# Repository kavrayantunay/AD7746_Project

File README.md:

# AD7746_Project
I shared this project in PCBWay community, if you want to get this project please check the link "https://www.pcbway.com/project/shareproject/AD7746_Project_023b445f.html"

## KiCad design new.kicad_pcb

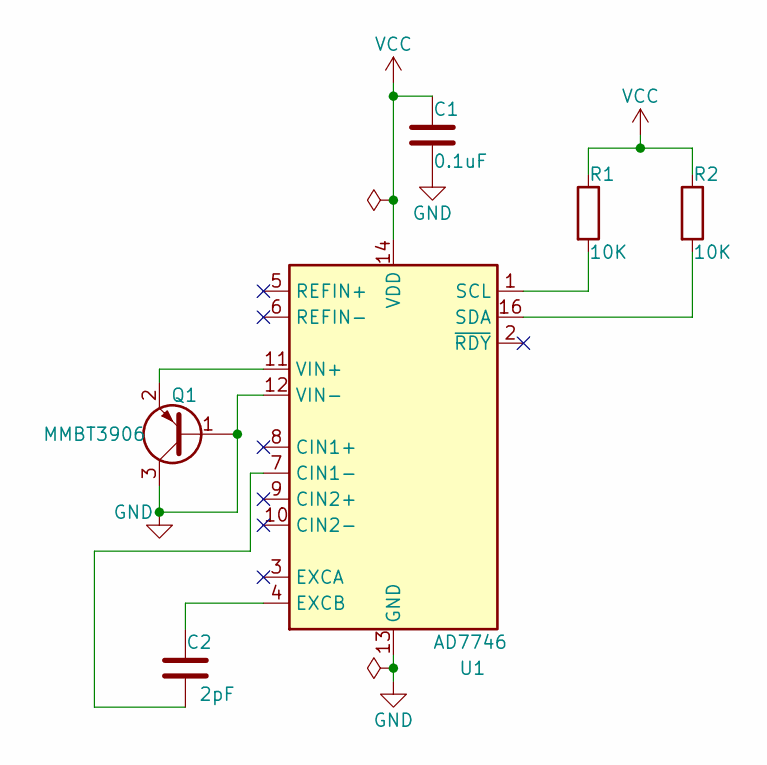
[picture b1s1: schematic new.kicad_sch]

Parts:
C1: 0.1uF
C2: 2pF
Q1: MMBT3906; SOT-23
R1, R2: 10K
U1: AD7746; TSSOP-16_4.4x5mm_P0.65mm

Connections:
GND: C1.2, Q1.1 (B), Q1.3 (C), U1.12 (VIN-), U1.13 (GND)
unnamed: C2.1, U1.4 (EXCB)
unnamed: C2.2, U1.7 (CIN1-)
unnamed: Q1.2 (E), U1.11 (VIN+)
unnamed: R1.2, U1.1 (SCL)
unnamed: R2.2, U1.16 (SDA)
VCC: C1.1, R1.1, R2.1, U1.14 (VDD)

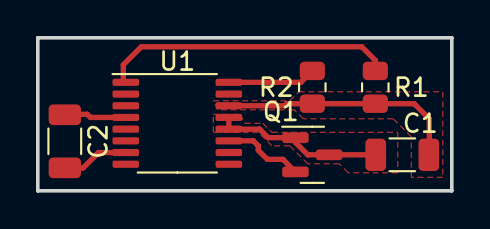
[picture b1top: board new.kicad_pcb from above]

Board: 2 copper layers, 23.0 x 8.5 mm, 6 parts (0 on the bottom side), 7 nets.
